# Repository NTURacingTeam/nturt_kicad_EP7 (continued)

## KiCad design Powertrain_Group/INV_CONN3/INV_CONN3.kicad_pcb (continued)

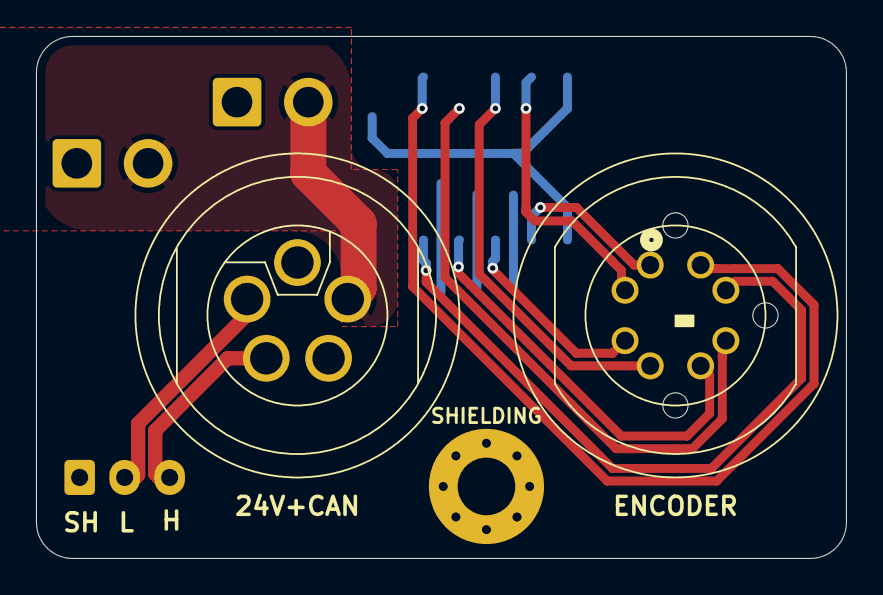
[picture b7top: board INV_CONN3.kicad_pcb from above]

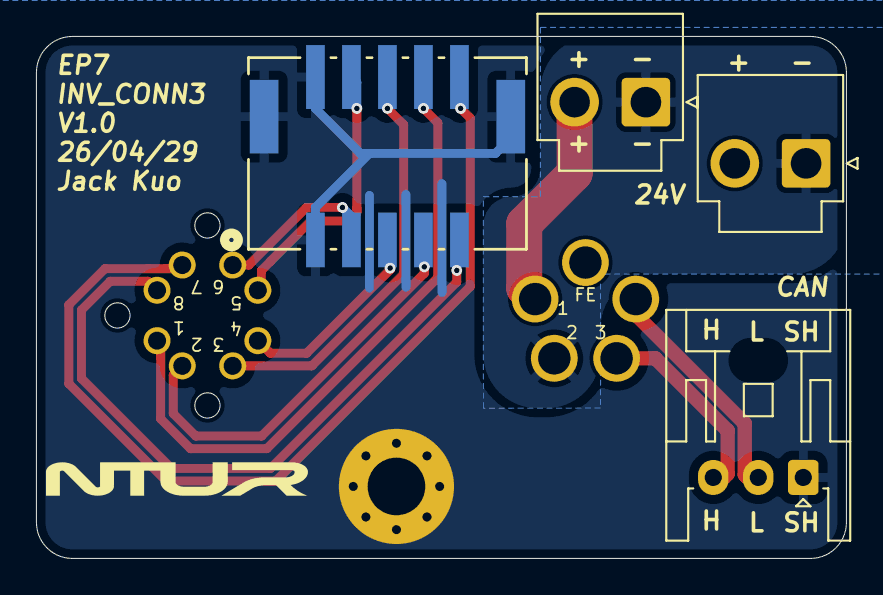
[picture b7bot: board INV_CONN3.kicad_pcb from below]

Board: 2 copper layers, 45.0 x 29.0 mm, 7 parts (4 on the bottom side), 13 nets.

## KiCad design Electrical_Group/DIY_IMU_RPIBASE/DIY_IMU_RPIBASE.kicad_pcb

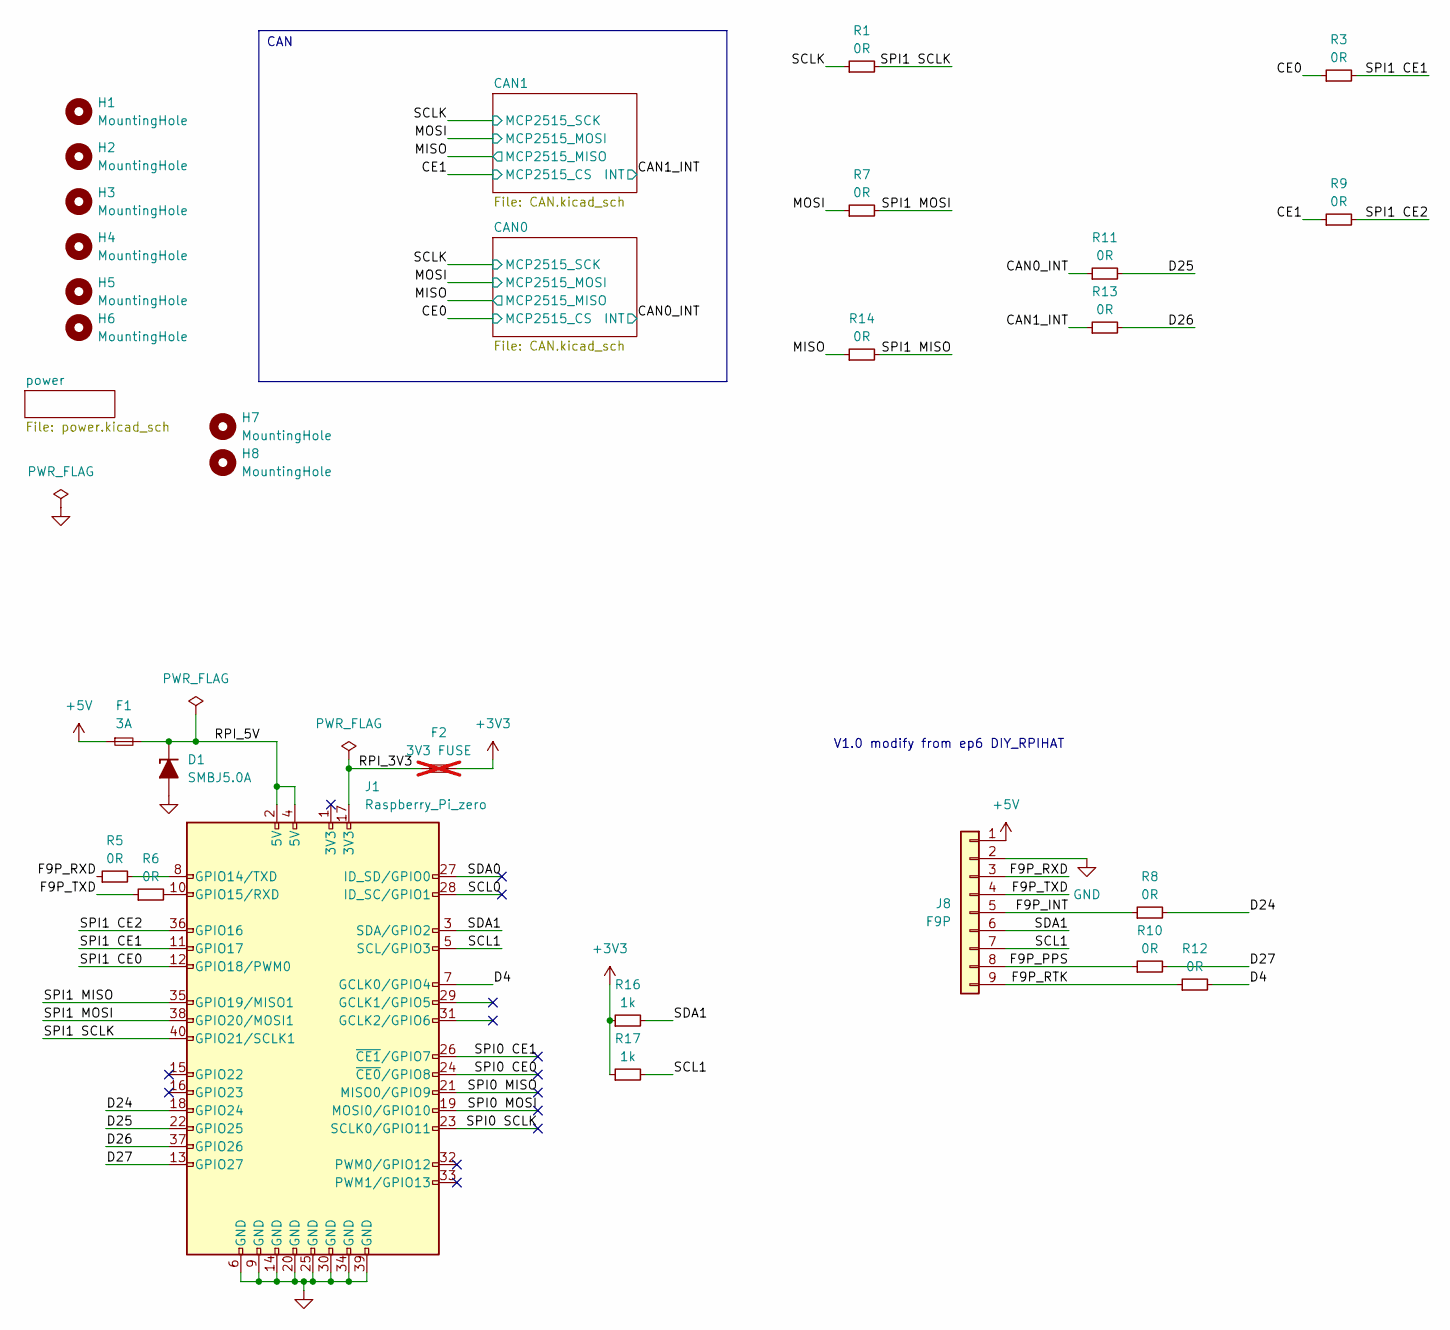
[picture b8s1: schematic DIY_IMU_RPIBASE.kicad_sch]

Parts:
D1: SMBJ5.0A; D_SMB
F1: 3A; Fuse_1206_3216Metric
F2: 3V3 FUSE; Fuse_1206_3216Metric; not fitted
H1, H2, H3, H4, H5, H6, H7, H8: MountingHole; MountingHole_2.7mm_M2.5
J1: Raspberry_Pi_zero; PinSocket_2x20_P2.54mm_Vertical
J8: F9P; PinSocket_1x09_P2.54mm_Vertical
R1, R3, R5, R6, R7, R8, R9, R10, R11, R12, R13, R14: 0R; R_0603_1608Metric
R16, R17: 1k; R_0603_1608Metric

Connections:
+3V3: F2.2, R16.1, R17.1; also elsewhere on the board
+5V: F1.1, J8.1; also elsewhere on the board
/CAN0_INT: R11.1; also elsewhere on the board
/CAN1_INT: R13.1; also elsewhere on the board
/CE0: R3.1; also elsewhere on the board
/CE1: R9.1; also elsewhere on the board
/D4: J1.7 (GCLK0/GPIO4), R12.2
/D5: J1.29 (GCLK1/GPIO5)
/D6: J1.31 (GCLK2/GPIO6)
/D22: J1.15 (GPIO22)
/D23: J1.16 (GPIO23)
/D24: J1.18 (GPIO24), R8.2
/D25: J1.22 (GPIO25), R11.2
/D26: J1.37 (GPIO26), R13.2
/D27: J1.13 (GPIO27), R10.2
/F9P_INT: J8.5, R8.1
/F9P_PPS: J8.8, R10.1
/F9P_RTK: J8.9, R12.1
/F9P_RXD: J8.3, R5.1
/F9P_TXD: J8.4, R6.1
/MISO: R14.1; also elsewhere on the board
/MOSI: R7.1; also elsewhere on the board
/RPI_3V3: F2.1, J1.17 (3V3)
/RPI_5V: D1.1 (K), F1.2, J1.2 (5V), J1.4 (5V)
/SCL0: J1.28 (ID_SC/GPIO1)
/SCL1: J1.5 (SCL/GPIO3), J8.7, R17.2
/SCLK: R1.1; also elsewhere on the board
/SDA0: J1.27 (ID_SD/GPIO0)
/SDA1: J1.3 (SDA/GPIO2), J8.6, R16.2
/SPI0 CE0: J1.24 (~CE0/GPIO8)
/SPI0 CE1: J1.26 (~CE1/GPIO7)
/SPI0 MISO: J1.21 (MISO0/GPIO9)
/SPI0 MOSI: J1.19 (MOSI0/GPIO10)
/SPI0 SCLK: J1.23 (SCLK0/GPIO11)
/SPI1 CE0: J1.12 (GPIO18/PWM0)
/SPI1 CE1: J1.11 (GPIO17), R3.2
/SPI1 CE2: J1.36 (GPIO16), R9.2
/SPI1 MISO: J1.35 (GPIO19/MISO1), R14.2
/SPI1 MOSI: J1.38 (GPIO20/MOSI1), R7.2
/SPI1 SCLK: J1.40 (GPIO21/SCLK1), R1.2
GND: D1.2 (A), J1.6 (GND), J1.9 (GND), J1.14 (GND), J1.20 (GND), J1.25 (GND), J1.30 (GND), J1.34 (GND), J1.39 (GND), J8.2; also elsewhere on the board
unnamed: J1.8 (GPIO14/TXD), R5.2
unnamed: J1.10 (GPIO15/RXD), R6.2

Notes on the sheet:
CAN
V1.0 modify from ep6 DIY_RPIHAT

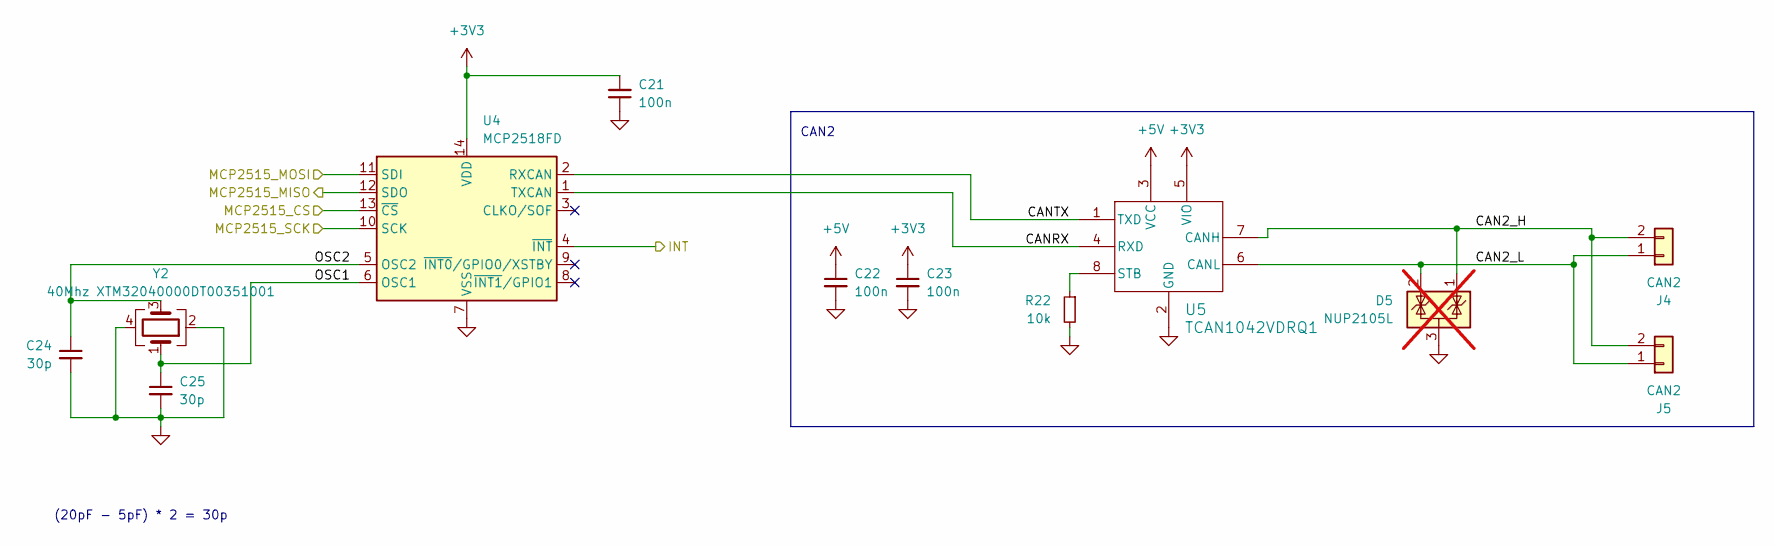
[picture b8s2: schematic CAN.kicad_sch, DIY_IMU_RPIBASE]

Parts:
C21, C22, C23: 100n; C_0603_1608Metric
C24, C25: 30p; C_0603_1608Metric
D5: NUP2105L; SOT-23; not fitted
J4, J5: CAN2; JST_XH_B2B-XH-A_1x02_P2.50mm_Vertical
R22: 10k; C_0603_1608Metric
U4: MCP2518FD; SOIC-14_3.9x8.7mm_P1.27mm
U5: TCAN1042VDRQ1; SOIC-8_3.9x4.9mm_P1.27mm
Y2: 40Mhz XTM32040000DT00351001; Crystal_SMD_3225-4Pin_3.2x2.5mm

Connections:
+3V3: C21.2, C23.1, U4.14 (VDD), U5.5 (VIO); also elsewhere on the board
+5V: C22.1, U5.3 (VCC); also elsewhere on the board
/CAN0/CAN2_H: D5.1 (K), J4.2, J5.2, U5.7 (CANH)
/CAN0/CAN2_L: D5.2 (K), J4.1, J5.1, U5.6 (CANL)
/CAN0/CANRX: U4.1 (TXCAN), U5.4 (RXD)
/CAN0/CANTX: U4.2 (RXCAN), U5.1 (TXD)
/CAN0/OSC1: C25.1, U4.6 (OSC1), Y2.1
/CAN0/OSC2: C24.1, U4.5 (OSC2), Y2.3
/CAN0_INT: U4.4 (~INT); also elsewhere on the board
/CE0: U4.13 (~CS); also elsewhere on the board
/MISO: U4.12 (SDO); also elsewhere on the board
/MOSI: U4.11 (SDI); also elsewhere on the board
/SCLK: U4.10 (SCK); also elsewhere on the board
GND: C21.1, C22.2, C23.2, C24.2, C25.2, D5.3 (A), R22.2, U4.7 (VSS), U5.2 (GND), Y2.2, Y2.4; also elsewhere on the board
unnamed: R22.1, U5.8 (STB)

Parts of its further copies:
C26, C27, C28: 100n; C_0603_1608Metric
C29, C30: 30p; C_0603_1608Metric
D6: NUP2105L; SOT-23; not fitted
J6, J7: CAN2; JST_XH_B2B-XH-A_1x02_P2.50mm_Vertical
R23: 10k; C_0603_1608Metric
U6: MCP2518FD; SOIC-14_3.9x8.7mm_P1.27mm
U7: TCAN1042VDRQ1; SOIC-8_3.9x4.9mm_P1.27mm
Y3: 40Mhz XTM32040000DT00351001; Crystal_SMD_3225-4Pin_3.2x2.5mm

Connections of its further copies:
+3V3: C26.2, C28.1, U6.14 (VDD), U7.5 (VIO); also elsewhere on the board
+5V: C27.1, U7.3 (VCC); also elsewhere on the board
/CAN1/CAN2_H: D6.1 (K), J6.2, J7.2, U7.7 (CANH)
/CAN1/CAN2_L: D6.2 (K), J6.1, J7.1, U7.6 (CANL)
/CAN1/CANRX: U6.1 (TXCAN), U7.4 (RXD)
/CAN1/CANTX: U6.2 (RXCAN), U7.1 (TXD)
/CAN1/OSC1: C30.1, U6.6 (OSC1), Y3.1
/CAN1/OSC2: C29.1, U6.5 (OSC2), Y3.3
/CAN1_INT: U6.4 (~INT); also elsewhere on the board
/CE1: U6.13 (~CS); also elsewhere on the board
/MISO: U6.12 (SDO); also elsewhere on the board
/MOSI: U6.11 (SDI); also elsewhere on the board
/SCLK: U6.10 (SCK); also elsewhere on the board
GND: C26.1, C27.2, C28.2, C29.2, C30.2, D6.3 (A), R23.2, U6.7 (VSS), U7.2 (GND), Y3.2, Y3.4; also elsewhere on the board
unnamed: R23.1, U7.8 (STB)

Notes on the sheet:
(20pF - 5pF) * 2 = 30p
CAN2

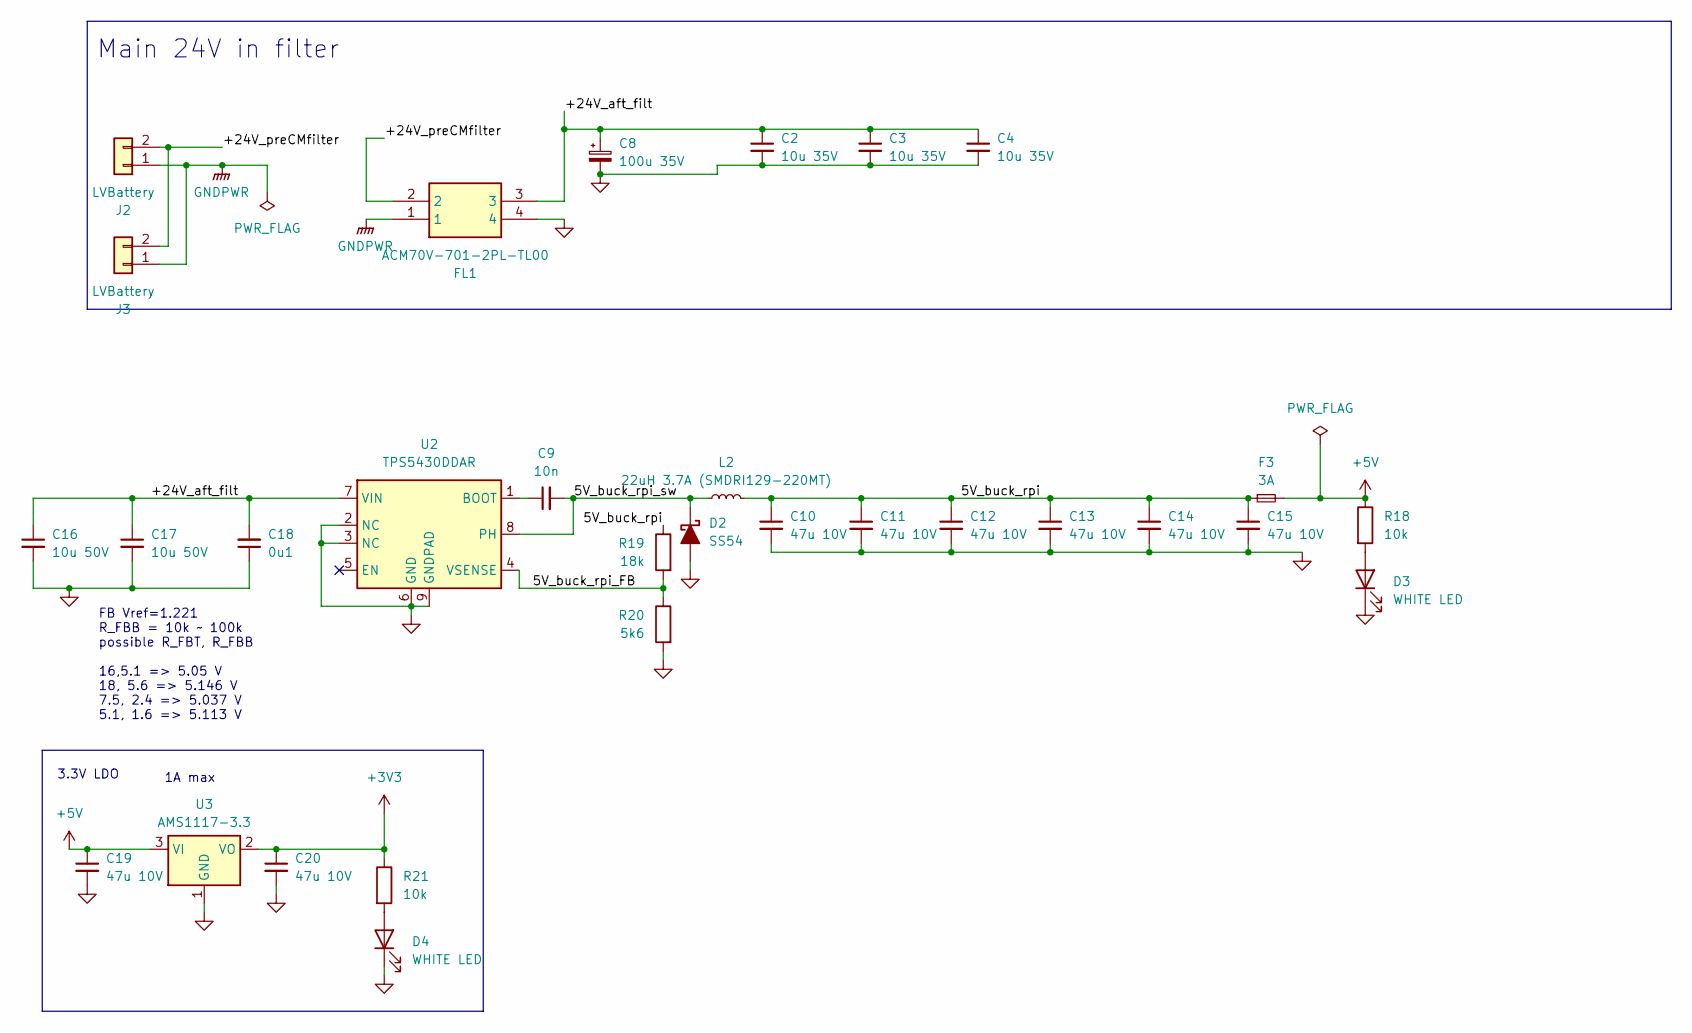
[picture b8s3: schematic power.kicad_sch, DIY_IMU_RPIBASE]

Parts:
C2, C3, C4: 10u 35V; C_1206_3216Metric
C8: 100u 35V; CP_Radial_D6.3mm_P2.50mm
C9: 10n; C_0603_1608Metric
C10, C11, C12, C13, C14, C15, C19, C20: 47u 10V; C_1206_3216Metric
C16, C17: 10u 50V; C_1206_3216Metric
C18: 0u1; C_0603_1608Metric
D2: SS54; D_SMA
D3, D4: WHITE LED; LED_0603_1608Metric
F3: 3A; Fuse_1206_3216Metric
FL1: ACM70V-701-2PL-TL00; ACM70V7012PLTL00; Mouser Part Number 810-ACM70V7012PLTL00
J2, J3: LVBattery; JST_XH_B2B-XH-A_1x02_P2.50mm_Vertical
L2: 22uH 3.7A (SMDRI129-220MT); L_Bourns_SRR1260
R18, R21: 10k; R_0603_1608Metric
R19: 18k; R_0603_1608Metric
R20: 5k6; R_0603_1608Metric
U2: TPS5430DDAR; TI_SO-PowerPAD-8_ThermalVias
U3: AMS1117-3.3; SOT-223-3_TabPin2

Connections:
+3V3: C20.1, R21.1, U3.2 (VO); also elsewhere on the board
+5V: C19.1, F3.2, R18.1, U3.3 (VI); also elsewhere on the board
/power/5V_buck_rpi: C10.1, C11.1, C12.1, C13.1, C14.1, C15.1, F3.1, L2.2, R19.1
/power/5V_buck_rpi_FB: R19.2, R20.1, U2.4 (VSENSE)
/power/5V_buck_rpi_sw: C9.2, D2.1 (K), L2.1, U2.8 (PH)
/power/+24V_aft_filt: C2.1, C3.1, C4.1, C8.1, C16.1, C17.1, C18.2, FL1.3, U2.7 (VIN)
/power/+24V_preCMfilter: FL1.2, J2.2, J3.2
GND: C2.2, C3.2, C4.2, C8.2, C10.2, C11.2, C12.2, C13.2, C14.2, C15.2, C16.2, C17.2, C18.1, C19.2, C20.2, D2.2 (A), D3.1 (K), D4.1 (K), FL1.4, R20.2, U2.2 (NC), U2.3 (NC), U2.6 (GND), U2.9 (GNDPAD), U3.1 (GND); also elsewhere on the board
GNDPWR: FL1.1, J2.1, J3.1
unnamed: D3.2 (A), R18.2
unnamed: D4.2 (A), R21.2
unnamed: C9.1, U2.1 (BOOT)

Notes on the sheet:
3.3V LDO
FB Vref=1.221 R_FBB = 10k ~ 100k possible R_FBT, R_FBB 16,5.1 => 5.05 V 18, 5.6 => 5.146 V 7.5, 2.4 => 5.037 V 5.1, 1.6 => 5.113 V
1A max
Main 24V in filter

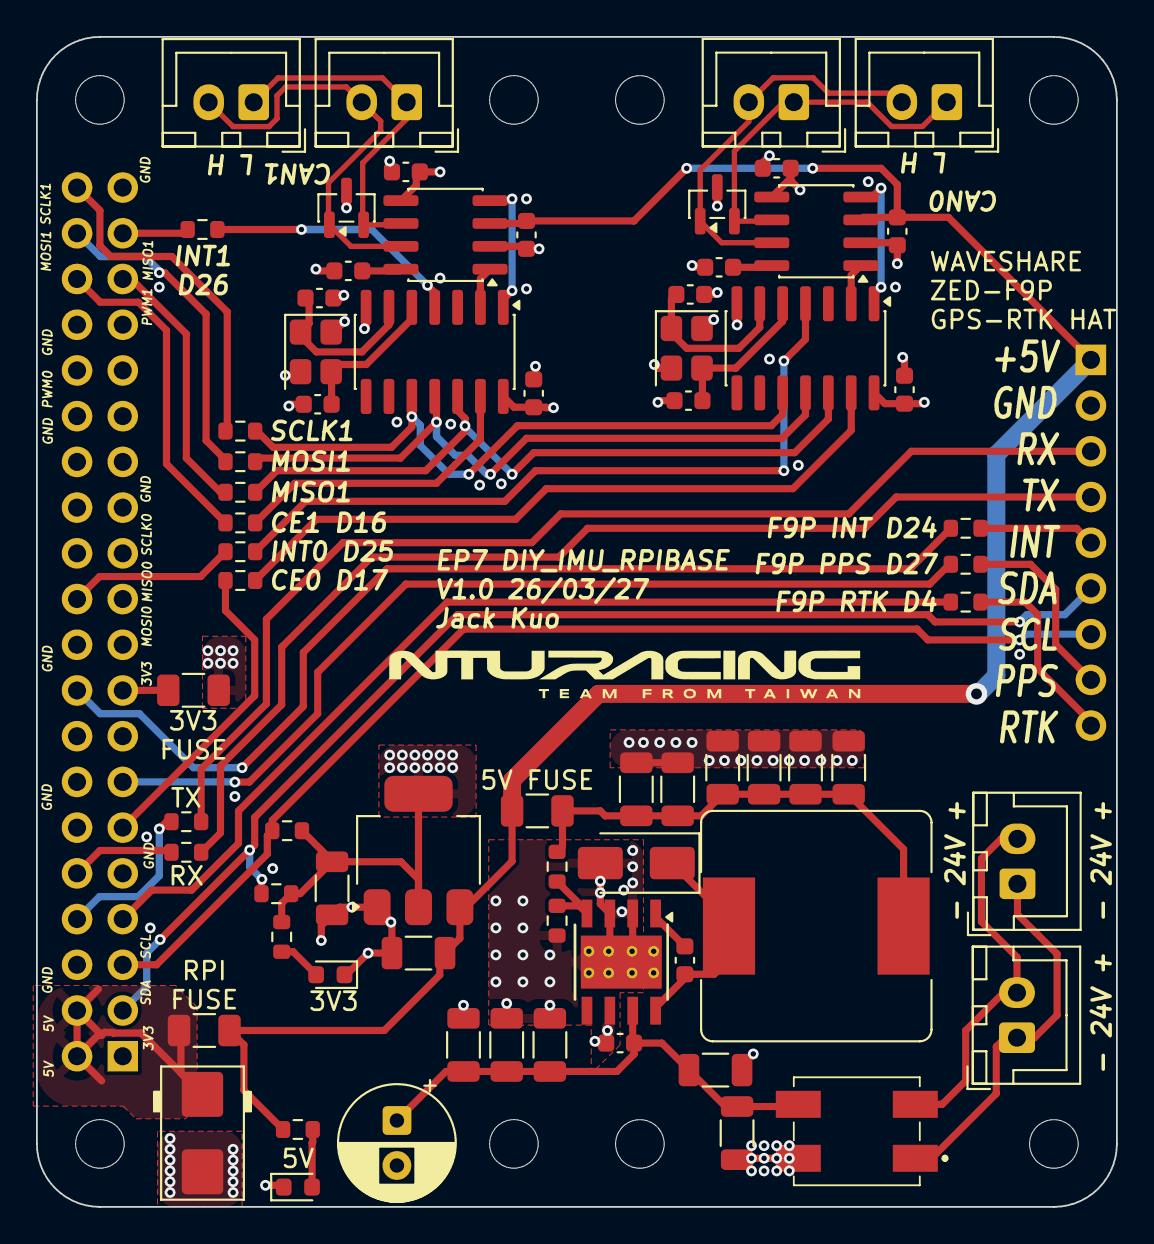
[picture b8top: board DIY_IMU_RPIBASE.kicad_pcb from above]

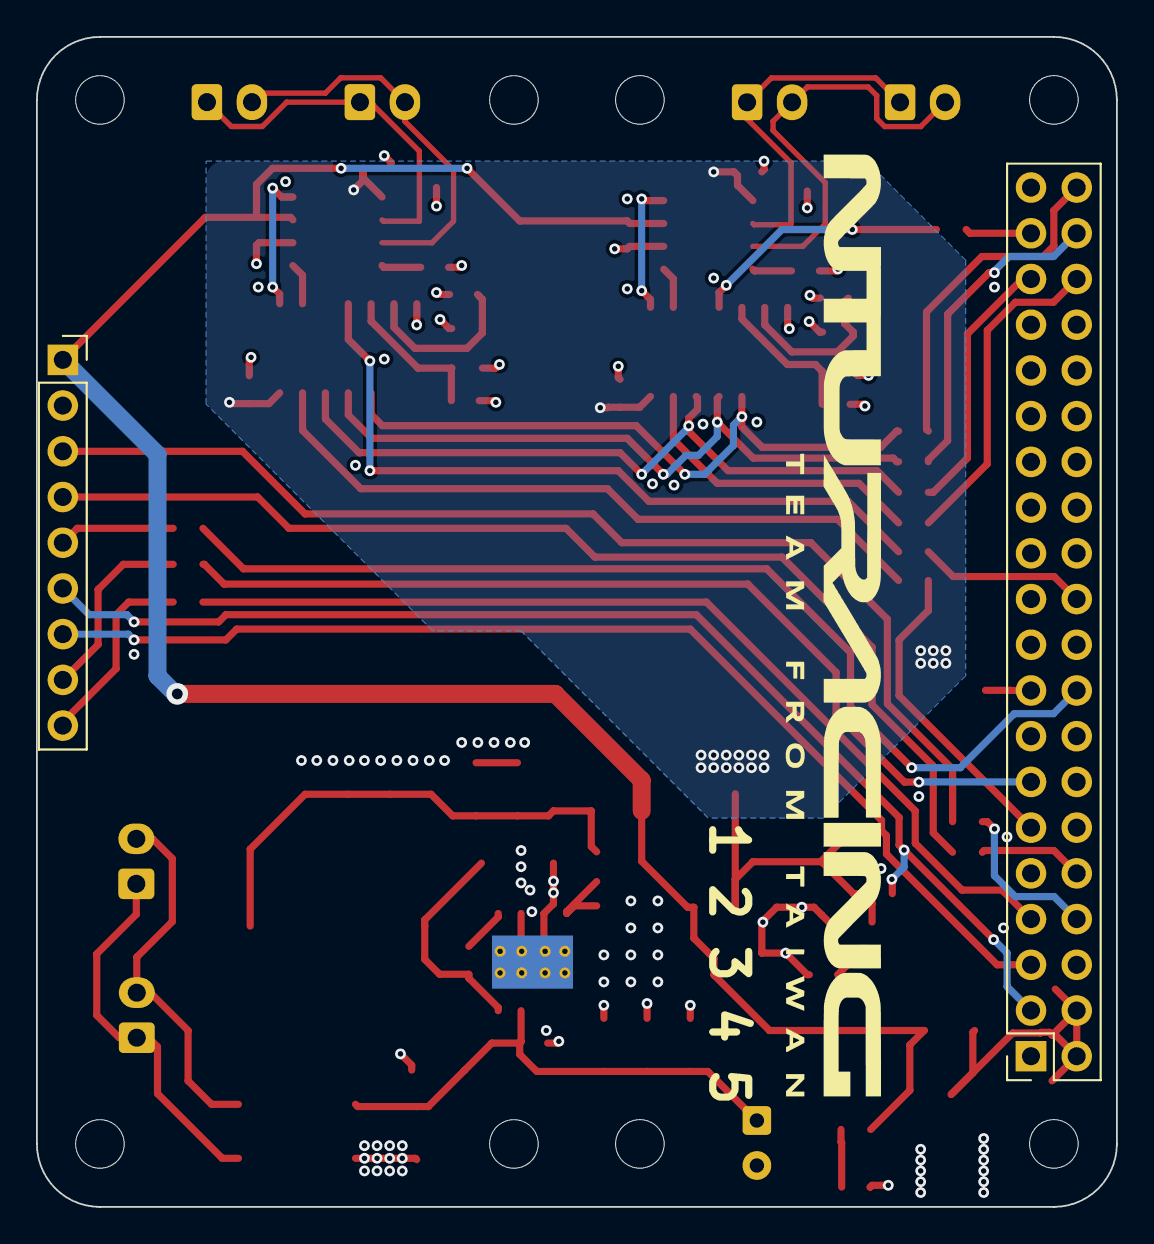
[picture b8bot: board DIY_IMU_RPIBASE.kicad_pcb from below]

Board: 4 copper layers, 60.0 x 65.0 mm, 81 parts (2 on the bottom side), 54 nets.

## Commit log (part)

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2026-02-24 init repo
    moved from the old nturt_kicad repo
    will act as submodule of nturt_kicad in the future
2026-02-24 [VCU_CM5] update to V1.0
    still needs many modifications
2026-02-24 update library
2026-02-25 [VCU_CM5] update to V1.2
2026-02-26 Embed fonts, update components
2026-02-26 [VCU_CM5] update fooprints
2026-02-28 [VCU_CM5] update to V1.3
2026-03-01 [Tire_Temp] V1.0
2026-03-02 [Steering_Panel] V1.0
2026-03-02 [Steering_Panel_Under] V1.0
2026-03-02 [INV_MotorTempIso] V1.0
2026-03-03 [INV_CONN1] V1.0
2026-03-04 [INV_CONN2] V1.0
2026-03-04 update library for molex micro lock plus
2026-03-04 [PCAN_PRO] V1.0
2026-03-04 [PCAN_PRO] V1.1
2026-03-05 [DIY_MGJ6] V1.0
2026-03-05 [DIY_MGJ6] V1.1 minor change
2026-03-06 [INV_Boost_Power] V1.0
    by shinkansen942
2026-03-06 [INV_Boost_Controller] V1.0
    by shinkansen942
2026-03-06 [INV_Boost_Iso] V1.1
2026-03-06 [INV_Bost_Isense] V1.1
2026-03-09 [INV_Boost_Controller] V1.1
2026-03-09 [INV_Boost_Iso] V1.2
    swap 0402 with 0603
2026-03-12 [INV_Discreete_Power] V1.0
2026-03-12 [INV_Discrete_Iso] V1.0 by LY Chen
2026-03-12 [INV_Discrete_Isense] V1.0 by LY Chen
2026-03-12 [INV_Discrete_Controller] V1.0 by LY Chen
2026-03-13 [INV_Discrete_Power] V1.1 by Jack Kuo
2026-03-13 [INV_Discrete_Power] V1.2
2026-03-13 [INV_Discrete_Iso] V1.1
2026-03-13 [INV_Discrete_Isense] V1.1
    and update library for it
2026-03-14 [INV_Discrete_Controller] V1.1
2026-03-15 [INV_Discrete_Isense] V1.2
2026-03-15 [PCAN_PRO] V1.1 again
    minor update for jlc
2026-03-15 [Tire_Temp] V1.0 again
    minor update for jlc
2026-03-15 [INV_Boost_Controller] V1.1 again
    minor update for jlc
2026-03-15 [INV_CONN1] V1.1
2026-03-15 [INV_CONN2] V1.1
2026-03-17 [INV_Discrete_Controller] V1.2
2026-03-17 [INV_Discete_Isense] V1.2 again
    change gain 1 to 2
2026-03-17 [INV_Discrete_Iso] V1.2
    fix connector to controller board mismatch
2026-03-17 [INV_Discrete_Isense] V1.2 again
    fix via intersect
2026-03-24 [INV_Discrete_Isense] V1.3
2026-05-04 update libraries
2026-05-04 [DIY_IMU_BASE] V1.0
2026-05-04 [DIY_IMU_RPIBASE] V1.0
2026-05-04 [MOT_Enc_TempIso] V1.0
2026-05-04 [INV_CONN3] V1.0
2026-05-21 [VCU_CM4] V1.0
    derived from VCU_CM5
2026-05-21 update library
    for cm4
2026-05-22 vcu_cm4 minor pcb adjustment
2026-06-03 [VCU_CM4] V1.1
2026-06-03 [VCU_CM4_CONN1] V1.0
2026-06-03 [Dash_Screen_Under] V1.1
2026-06-03 [Dash_Screen] V1.0
2026-06-03 [DEV_UPS] V1.0
2026-06-23 [Dash_Screen] V2.0
2026-06-23 [Dash_Screen_Under] V2.0
